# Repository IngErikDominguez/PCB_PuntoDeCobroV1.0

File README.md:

# PCB_PuntoDeCobroV1.0
Diseño del primer PCB de punto de cobro

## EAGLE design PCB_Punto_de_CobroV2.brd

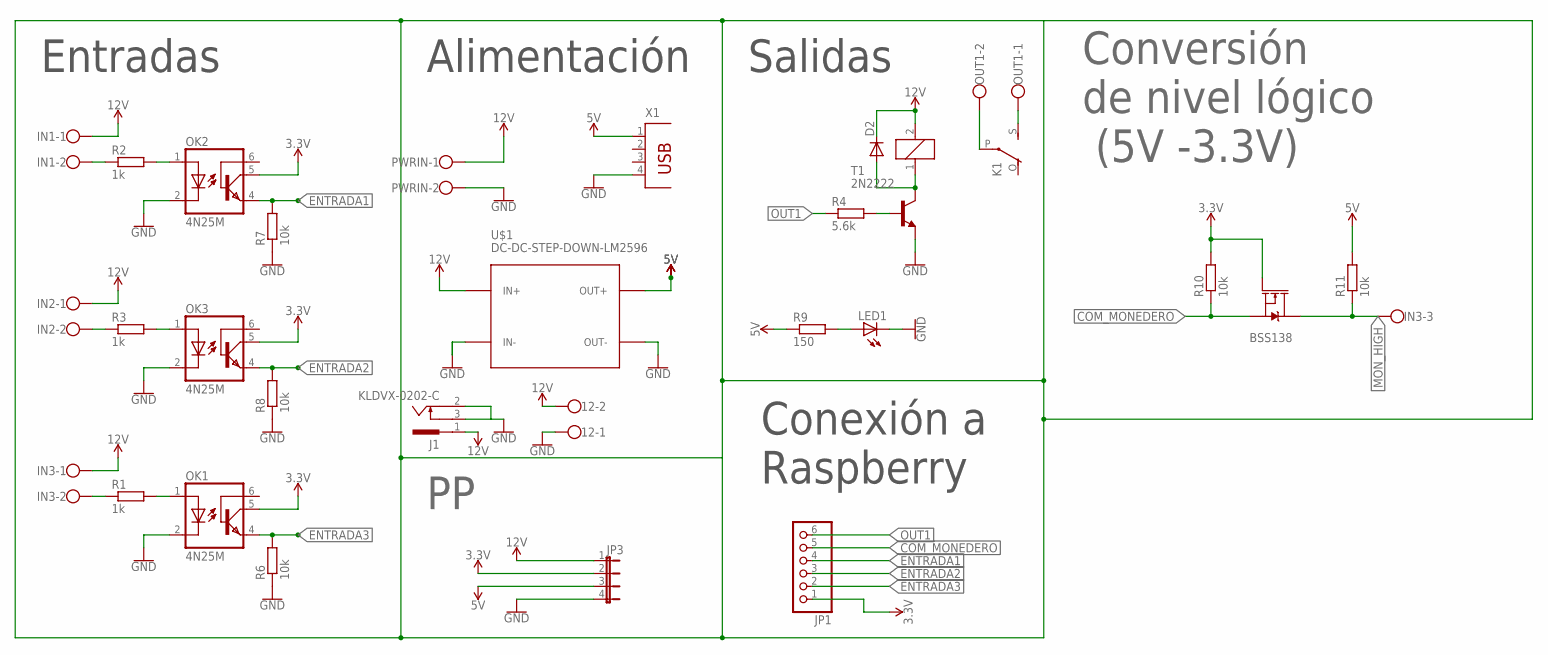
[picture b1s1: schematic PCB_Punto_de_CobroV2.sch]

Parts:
12: W237-102
D2: 1N4148DO35-7; DO35-7
IN1, IN2: W237-102
IN3: W237-103
J1: KLDVX-0202-C
JP1: PINHD-1X6; 1X06
JP3: JP4E; JP4
K1: G5L; G5LE
LED1: LED5MM
OK1, OK2, OK3: 4N25M; DIL06
OUT1: W237-102
PWRIN: W237-102
Q3: BSS138; SOT23-3
R1, R2, R3: 1k; 0204/7
R4: 5.6k; 0204/7
R6, R7, R8, R10, R11: 10k; 0204/7
R9: 150; 0204/7
T1: 2N2222; TO18
U$1: DC-DC-STEP-DOWN-LM2596
X1: PN87520

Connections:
3.3V: JP1.1, JP3.2, OK1.5 (COL), OK2.5 (COL), OK3.5 (COL), Q3.1 (G), R10.2
5V: JP3.3, R9.1, R11.2, U$1.OUT+, X1.1
12V: 12.2, D2.C, IN1.1, IN2.1, IN3.1, J1.1, JP3.1, K1.2, PWRIN.1, U$1.IN+
COM_MONEDERO: JP1.5, Q3.2 (S), R10.1
ENTRADA1: JP1.4, OK2.4 (EMI), R7.2
ENTRADA2: JP1.3, OK3.4 (EMI), R8.2
ENTRADA3: JP1.2, OK1.4 (EMI), R6.2
GND: 12.1, J1.2, J1.3, JP3.4, LED1.K (C), OK1.2 (C), OK2.2 (C), OK3.2 (C), PWRIN.2, R6.1, R7.1, R8.1, T1.1 (E), U$1.IN-, U$1.OUT-, X1.4
MON_HIGH: IN3.3, Q3.3 (D), R11.1
unnamed: OK1.1 (A), R1.2
unnamed: IN2.2, R3.1
unnamed: OK2.1 (A), R2.2
unnamed: IN1.2, R2.1
unnamed: OK3.1 (A), R3.2
unnamed: IN3.2, R1.1
unnamed: R4.2, T1.2 (B)
unnamed: D2.A, K1.1, T1.3 (C)
unnamed: LED1.A, R9.2
unnamed: K1.P, OUT1.2
unnamed: K1.S, OUT1.1
OUT1: JP1.6, R4.1

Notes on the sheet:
Entradas
Salidas
Alimentación
Conexión a Raspberry
Conversión de nivel lógico (5V -3.3V)

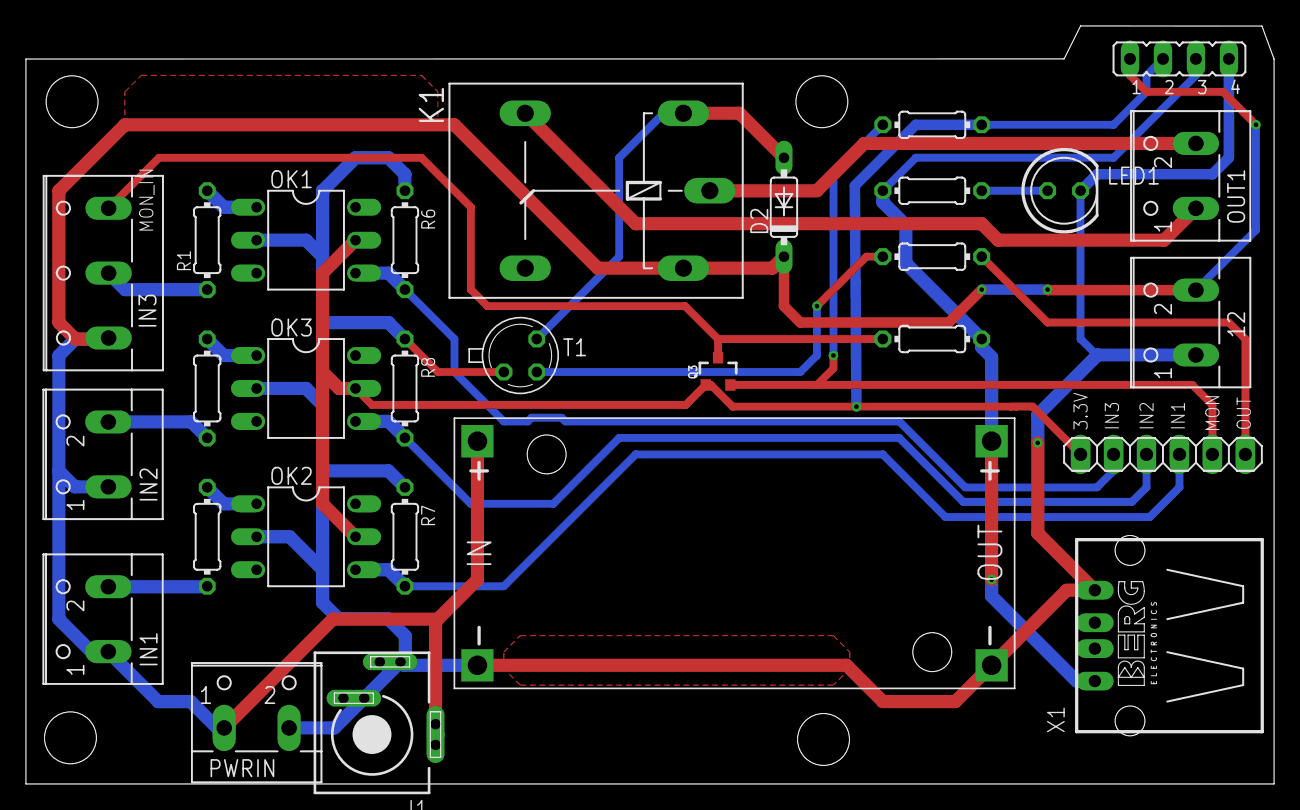
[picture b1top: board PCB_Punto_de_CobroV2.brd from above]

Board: 2 copper layers, 96.2 x 58.4 mm, 29 parts (0 on the bottom side), 21 nets.

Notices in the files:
parts and their libraries:
SparkFun-DiscreteSemi: Licensing: Creative Commons ShareAlike 4.0 International - https://creativecommons.org/licenses/by-sa/4.0
diy-modules: Released under the Creative Commons Attribution 4.0 International License: http://creativecommons.org/licenses/by/4.0
